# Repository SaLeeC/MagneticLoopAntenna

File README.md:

# MagneticLoopAntenna
A controll sistem for a Magnetic Loop Antenna

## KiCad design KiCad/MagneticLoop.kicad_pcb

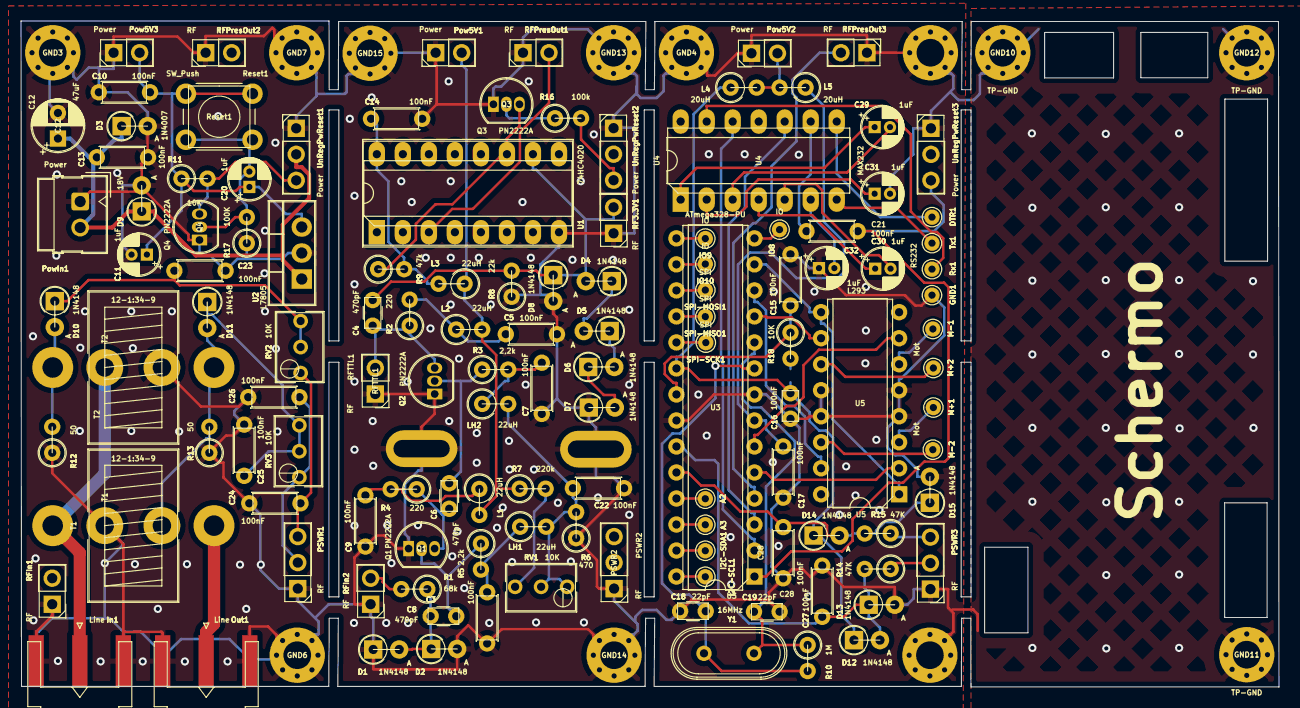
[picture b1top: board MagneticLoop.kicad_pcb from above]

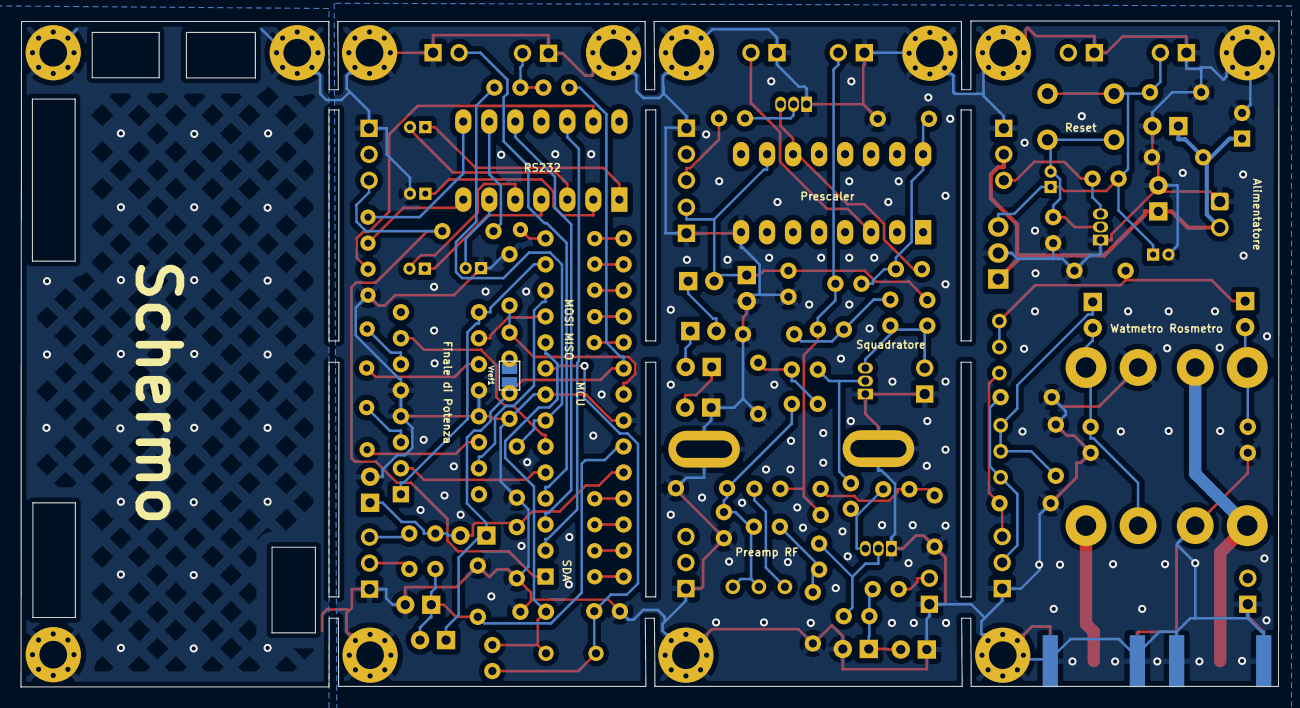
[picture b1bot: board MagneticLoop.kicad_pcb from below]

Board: 2 copper layers, 122.8 x 65.0 mm, 138 parts (2 on the bottom side), 79 nets.

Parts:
A2, A3: An; TestPoint_THTPad_D1.5mm_Drill0.7mm
C3, C4, C6: 470pF; C_Disc_D3.0mm_W1.6mm_P2.50mm
C5, C7, C8, C9, C10, C13, C14, C15, C17, C21, C22, C23, C24, C25, C26, C27, C28: 100nF; C_Disc_D4.3mm_W1.9mm_P5.00mm
C11, C20, C29, C30, C31, C32: 1uF; CP_Radial_D4.0mm_P1.50mm
C12: 47uF; CP_Radial_D5.0mm_P2.50mm
C16: 100nF; C_Disc_D3.0mm_W1.6mm_P2.50mm
C18, C19: 22pF; C_Disc_D3.0mm_W1.6mm_P2.50mm
D1, D2, D4, D5, D6, D7, D8, D10, D11, D12, D13, D14, D15: 1N4148; D_A-405_P2.54mm_Vertical_AnodeUp
D3: 1N4007; D_A-405_P2.54mm_Vertical_AnodeUp
D9: 18V; D_A-405_P2.54mm_Vertical_AnodeUp
DTR1: RS232; TestPoint_THTPad_D1.5mm_Drill0.7mm
GND1: RS232; TestPoint_THTPad_D1.5mm_Drill0.7mm
GND2, GND8: TP-GND; Asola
GND3, GND4, GND5, GND6, GND7, GND10, GND11, GND12, GND13, GND14, GND15, GND16: TP-GND; MountingHole_2.7mm_M2.5_Pad_Via
I2C-SCL1, I2C-SDA1: I2C; TestPoint_THTPad_D1.5mm_Drill0.7mm
IO8, IO9, IO10: IO; TestPoint_THTPad_D1.5mm_Drill0.7mm
In1: Line; SMA_Amphenol_132289_EdgeMount
L1, L2, L3: 22uH; L_Axial_L6.6mm_D2.7mm_P2.54mm_Vertical_Vishay_IM-2
L4, L5: 20uH; L_Axial_L6.6mm_D2.7mm_P2.54mm_Vertical_Vishay_IM-2
LH1, LH2: 22uH; L_Axial_L6.6mm_D2.7mm_P2.54mm_Vertical_Vishay_IM-2
M+1, M+2: Mot; TestPoint_THTPad_D1.5mm_Drill0.7mm
M-1, M-2: Mot; TestPoint_THTPad_D1.5mm_Drill0.7mm
Out1: Line; SMA_Amphenol_132289_EdgeMount
PSWR1, PSWR2, PSWR3: RF; PinHeader_1x03_P2.54mm_Vertical
Pow5V1, Pow5V2, Pow5V3: Power; PinHeader_1x02_P2.54mm_Vertical
PowIn1: Power; Molex_SL_171971-0002_1x02_P2.54mm_Vertical
Q1, Q2, Q3, Q4: PN2222A; TO-92_Inline
R1: 68k; R_Axial_DIN0207_L6.3mm_D2.5mm_P2.54mm_Vertical
R2, R4: 220; R_Axial_DIN0207_L6.3mm_D2.5mm_P2.54mm_Vertical
R3, R5: 2,2k; R_Axial_DIN0207_L6.3mm_D2.5mm_P2.54mm_Vertical
R6: 470; R_Axial_DIN0207_L6.3mm_D2.5mm_P2.54mm_Vertical
R7: 220k; R_Axial_DIN0207_L6.3mm_D2.5mm_P2.54mm_Vertical
R8: 22k; R_Axial_DIN0207_L6.3mm_D2.5mm_P2.54mm_Vertical
R9: 47k; R_Axial_DIN0207_L6.3mm_D2.5mm_P2.54mm_Vertical
R10: 1M; R_Axial_DIN0207_L6.3mm_D2.5mm_P2.54mm_Vertical
R11, R18: 10K; R_Axial_DIN0207_L6.3mm_D2.5mm_P2.54mm_Vertical
R12, R13: 50; R_Axial_DIN0207_L6.3mm_D2.5mm_P2.54mm_Vertical
R14, R15: 47K; R_Axial_DIN0207_L6.3mm_D2.5mm_P2.54mm_Vertical
R16: 100k; R_Axial_DIN0207_L6.3mm_D2.5mm_P2.54mm_Vertical
R17: 100K; R_Axial_DIN0207_L6.3mm_D2.5mm_P2.54mm_Vertical
RF3.3V1: RF; PinHeader_1x02_P2.54mm_Vertical
RFIn1, RFIn2: RF; PinHeader_1x02_P2.54mm_Vertical
RFPresOut1, RFPresOut2, RFPresOut3: RF; PinHeader_1x02_P2.54mm_Vertical
RFTTL1: RF; PinHeader_1x02_P2.54mm_Vertical
RV1, RV2, RV3: 10K; Potentiometer_Bourns_3266Y_Vertical
Reset1: SW_Push; SW_PUSH_6mm
Rx1: RS232; TestPoint_THTPad_D1.5mm_Drill0.7mm
SPI-MISO1: SPI; TestPoint_THTPad_D1.5mm_Drill0.7mm
SPI-MOSI1: SPI; TestPoint_THTPad_D1.5mm_Drill0.7mm
SPI-SCK1: SPI; TestPoint_THTPad_D1.5mm_Drill0.7mm
T1, T2: 12-1:34-9; L_Toroid_4Pin_Vertical_L14.7mm_W8.6mm_P5.58mm_Pulse_KM-1
Tx1: RS232; TestPoint_THTPad_D1.5mm_Drill0.7mm
U1: 74HC4020; DIP-16_W7.62mm_Socket_LongPads
U2: L7805; TO-220-3_Vertical
U3: ATmega328-PU; DIP-28_W7.62mm
U4: MAX232; DIP-14_W7.62mm_LongPads
U5: L293; DIP-16_W7.62mm
UnRegPwReset1, UnRegPwReset2, UnRegPwReset3: Power; PinHeader_1x03_P2.54mm_Vertical
Vref1: Vref; SolderJumper-2_P1.3mm_Open_Pad1.0x1.5mm
Y1: 16MHz; Crystal_HC49-U_Vertical

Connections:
/AccordatoreLoopCPU/Reset: C21.1, U3.1 (~RESET/PC6), UnRegPwReset3.3
/AccordatoreLoopCPU/Rx: U3.2 (PD0), U4.12 (R1OUT)
/AccordatoreLoopCPU/Tx: U3.3 (PD1), U4.10 (T2IN)
/AccordatoreLoopCPU/Xtal1: C18.2, R10.2, U3.9 (XTAL1/PB6), Y1.1
/AccordatoreLoopCPU/Xtal2: C19.2, R10.1, U3.10 (XTAL2/PB7), Y1.2
GND: C5.2, C7.2, C8.2, C9.2, C10.2, C11.2, C12.2, C13.2, C14.2, C15.1, C16.1, C17.1, C18.1, C19.1, C22.1, C23.2, C24.1, C25.2, C26.1, C27.1, C28.1, C31.2, C32.1, D1.1 (K), D2.2 (A), D3.2 (A), D7.1 (K), D8.2 (A), D9.2 (A), D13.2 (A), D15.2 (A), GND1.1, GND2.1, GND3.1, GND4.1, GND5.1, GND6.1, GND7.1, GND8.1, GND10.1, GND11.1, GND12.1, GND13.1, GND14.1, GND15.1, GND16.1, In1.2 (Ext), Out1.2 (Ext), PSWR1.1, PSWR2.1, PSWR3.1, Pow5V1.1, Pow5V2.1, Pow5V3.1, PowIn1.1, Q1.1 (E), Q2.1 (E), Q3.1 (E), Q4.1 (E), R6.1, R8.1, R12.1, R13.1, R17.1, RF3.3V1.1, RFIn1.1, RFIn2.1, RFPresOut1.1, RFPresOut2.1, RFPresOut3.1, RFTTL1.1, T1.4 (SB), T2.3 (SA), U1.8 (VSS), U2.2 (GND), U3.8 (GND), U3.22 (GND), U5.4 (GND), U5.5 (GND), U5.12 (GND), U5.13 (GND), UnRegPwReset1.1, UnRegPwReset2.1, UnRegPwReset3.1
unnamed: A2.1, U3.25 (PC2)
unnamed: A3.1, U3.26 (PC3)
unnamed: C3.1, Q1.2 (B), R5.1
unnamed: C3.2, D1.2 (A), D2.1 (K), R1.1
unnamed: C4.1, D4.2 (A), D8.1 (K), R8.2, RF3.3V1.2, U1.10 (CLK)
unnamed: C4.2, Q2.3 (C), R2.1, RFTTL1.2
unnamed: C5.1, L2.1, R2.2
unnamed: C6.1, Q2.2 (B), R3.1
unnamed: C6.2, Q1.3 (C), R4.1
unnamed: C7.1, LH2.1, R3.2
unnamed: C8.1, LH1.1, R5.2
unnamed: C9.1, L1.1, R4.2
unnamed: C10.1, C11.1, C20.1, Pow5V3.2, R11.1, Reset1.1, U2.3 (OUT)
unnamed: C12.1, C13.1, D3.1 (K), D9.1 (K), PowIn1.2, U2.1 (IN), UnRegPwReset1.2
unnamed: C14.1, L3.2, R9.2, U1.16 (VDD)
unnamed: C16.2, D12.1 (K), D14.1 (K), L4.1, U3.20 (AVCC), Vref1.1 (A)
unnamed: C17.2, L5.1, U3.7 (VCC)
unnamed: C21.2, U4.9 (R2OUT)
unnamed: C22.2, LH1.2, LH2.2, R6.2, RV1.1, RV1.2
unnamed: C23.1, D10.1 (K), RV2.2, RV2.3
unnamed: C24.2, PSWR1.3, RV2.1
unnamed: C25.1, D11.1 (K), RV3.2, RV3.3
unnamed: C26.2, PSWR1.2, RV3.1
unnamed: D4.1 (K), D5.2 (A)
unnamed: D5.1 (K), D6.2 (A)
unnamed: D6.1 (K), D7.2 (A)
unnamed: D10.2 (A), R12.2, T2.1 (AA)
unnamed: D11.2 (A), R13.2, T1.3 (SA), T2.2 (AB)
unnamed: DTR1.1, U4.8 (R2IN)
unnamed: I2C-SCL1.1, U3.28 (PC5)
unnamed: I2C-SDA1.1, U3.27 (PC4)
unnamed: IO8.1, U3.14 (PB0)
unnamed: IO9.1, U3.15 (PB1)
unnamed: IO10.1, U3.16 (PB2)
unnamed: In1.1 (In), T1.1 (AA), T2.4 (SB)
unnamed: L1.2, L2.2, L3.1, Pow5V1.2, R7.1
unnamed: L4.2, L5.2, Pow5V2.2
unnamed: M+1.1, U5.3 (1Y)
unnamed: M+2.1, U5.11 (3Y)
unnamed: M-1.1, U5.6 (2Y)
unnamed: M-2.1, U5.14 (4Y)
unnamed: Out1.1 (In), T1.2 (AB)
unnamed: PSWR3.2, R14.1
unnamed: PSWR3.3, R15.1
unnamed: Q3.2 (B), R16.1
unnamed: R1.2, RFIn2.2
unnamed: R7.2, RV1.3
unnamed: Q4.3 (C), R11.2, UnRegPwReset1.3
unnamed: RFPresOut1.2, U1.3 (Q13)
unnamed: RFPresOut3.2, U3.4 (PD2)
unnamed: C20.2, Q4.2 (B), R17.2, Reset1.2
unnamed: Rx1.1, U4.13 (R1IN)
unnamed: SPI-MISO1.1, U3.18 (PB4)
unnamed: SPI-MOSI1.1, U3.17 (PB3)
unnamed: SPI-SCK1.1, U3.19 (PB5)
unnamed: Tx1.1, U4.7 (T2OUT)
unnamed: Q3.3 (C), R9.1, U1.11 (Reset)
unnamed: U3.5 (PD3), U5.2 (1A)
unnamed: U3.6 (PD4), U5.7 (2A)
unnamed: U3.11 (PD5), U5.10 (3A)
unnamed: U3.12 (PD6), U5.15 (4A)
unnamed: U3.13 (PD7), U5.1 (EN1,2), U5.9 (EN3,4)
unnamed: C15.2, R18.1, U3.21 (AREF)
unnamed: C27.2, D12.2 (A), D13.1 (K), R14.2, U3.23 (PC0)
unnamed: C28.2, D14.2 (A), D15.1 (K), R15.2, U3.24 (PC1)
unnamed: C29.1, U4.1 (C1+)
unnamed: C31.1, U4.2 (VS+)
unnamed: C29.2, U4.3 (C1-)
unnamed: C30.1, U4.4 (C2+)
unnamed: C30.2, U4.5 (C2-)
unnamed: C32.2, U4.6 (VS-)
unnamed: R16.2, UnRegPwReset2.3
unnamed: R18.2, Vref1.2 (B)

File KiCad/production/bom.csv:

Designator,Footprint,Quantity,Value,LCSC Part #
"A0, A1, A2, A3",TestPoint_THTPad_D1.5mm_Drill0.7mm,4,An,
"C10, C13, C14, C15, C21, C22, C23, C24, C25, C26, C5, C7, C8, C9",C_Disc_D4.3mm_W1.9mm_P5.00mm,14,100nF,
"C11, C20",CP_Radial_D4.0mm_P1.50mm,2,1uF,
C12,CP_Radial_D5.0mm_P2.50mm,1,47uF,
"C16, C17",C_Disc_D3.0mm_W1.6mm_P2.50mm,2,100nF,
"C18, C19",C_Disc_D3.0mm_W1.6mm_P2.50mm,2,22pF,
"C3, C4, C6",C_Disc_D3.0mm_W1.6mm_P2.50mm,3,470pF,
"D1, D10, D11, D2, D4, D5, D6, D7, D8",D_A-405_P2.54mm_Vertical_AnodeUp,9,1N4148,
D3,D_A-405_P2.54mm_Vertical_AnodeUp,1,1N4007,
D9,D_A-405_P2.54mm_Vertical_AnodeUp,1,18V,
"DTR1, Rx1_2, Rx1, Tx1",TestPoint_THTPad_D1.5mm_Drill0.7mm,4,RS232,
"GND10, GND11, GND12, GND13, GND14, GND15, GND16, GND3, GND4, GND5, GND6, GND7",MountingHole_2.7mm_M2.5_Pad_Via,12,TP-GND,
"GND2, GND8",Asola,2,TP-GND,
"I2C-SCL1, I2C-SDA1",TestPoint_THTPad_D1.5mm_Drill0.7mm,2,I2C,
"IO10, IO3, IO4, IO5, IO6, IO7, IO8, IO9",TestPoint_THTPad_D1.5mm_Drill0.7mm,8,IO,
"In1, Out1",SMA_Amphenol_132289_EdgeMount,2,Line,
"InTTL1, PresOUT1",TestPoint_Loop_D2.50mm_Drill1.0mm,2,TTL-RF,
"L1, L2, L3, LH1, LH2",L_Axial_L6.6mm_D2.7mm_P2.54mm_Vertical_Vishay_IM-2,5,22uH,
"L4, L5",L_Axial_L6.6mm_D2.7mm_P2.54mm_Vertical_Vishay_IM-2,2,20uH,
"PSWR1, PSWR2, PSWR3",PinHeader_1x03_P2.54mm_Vertical,3,RF,
"Pow5V1, Pow5V2, Pow5V3, Pow5V4",PinHeader_1x02_P2.54mm_Vertical,4,Power,
PowIn1,Molex_SL_171971-0002_1x02_P2.54mm_Vertical,1,Power,
"Q1, Q2",TO-92_Inline,2,PN2222A,
R1,R_Axial_DIN0207_L6.3mm_D2.5mm_P2.54mm_Vertical,1,68k,
R10,R_Axial_DIN0207_L6.3mm_D2.5mm_P2.54mm_Vertical,1,1M,
R11,R_Axial_DIN0207_L6.3mm_D2.5mm_P2.54mm_Vertical,1,10K,
"R12, R13",R_Axial_DIN0207_L6.3mm_D2.5mm_P2.54mm_Vertical,2,50,
"R2, R4",R_Axial_DIN0207_L6.3mm_D2.5mm_P2.54mm_Vertical,2,220,
"R3, R5",R_Axial_DIN0207_L6.3mm_D2.5mm_P2.54mm_Vertical,2,"2,2k",
R6,R_Axial_DIN0207_L6.3mm_D2.5mm_P2.54mm_Vertical,1,470,
"R7, R9_2, R9",R_Axial_DIN0207_L6.3mm_D2.5mm_P2.54mm_Vertical,3,220k,
R8,R_Axial_DIN0207_L6.3mm_D2.5mm_P2.54mm_Vertical,1,22k,
"RF3.3V1, RFIn1, RFIn2, RFPresOut1, RFPresOut2, RFPresOut3, RFTTL1",PinHeader_1x02_P2.54mm_Vertical,7,RF,
RLSerieParallelo1,Relay_DPDT_Omron_G2RL,1,G2RL-2-ASI-DC5,
"RV1, RV2, RV3",Potentiometer_Bourns_3266Y_Vertical,3,10K,
Reset1,SW_PUSH_6mm,1,SW_Push,
"SPI-MISO1, SPI-MOSI1, SPI-SCK1",TestPoint_THTPad_D1.5mm_Drill0.7mm,3,SPI,
"T1, T2",L_Toroid_4Pin_Vertical_L14.7mm_W8.6mm_P5.58mm_Pulse_KM-1,2,12-1:34-9,
U1,DIP-16_W7.62mm_Socket_LongPads,1,74HC4020,
U2,TO-220-3_Vertical,1,L7805,
U3,DIP-28_W7.62mm,1,ATmega328-PU,
U4,SO-16_5.3x10.2mm_P1.27mm,1,MAX232,
"UnRegPwReset1, UnRegPwReset2, UnRegPwReset3",PinHeader_1x03_P2.54mm_Vertical,3,Power,
Y1,Crystal_HC49-U_Vertical,1,16MHz,
